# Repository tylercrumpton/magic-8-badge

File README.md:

# Magic 8-Badge

_Hardware, software, and other resouces for a fun little CircuitPython-compatible PCB badge!_

**Note:** Lots of information and improvements to be added soon!

## Hardware

All of the hardware design files are included in the [`hardware/`](./hardware) directory. The board was designed with KiCad 7, using mostly components from JLCPCB's [Assembly Parts Library](https://jlcpcb.com/parts).

## Firmware

The Magic 8-Badge was created to utilize [Adafruit's CircuitPython 🐍](https://circuitpython.org), and will hopefully have a board definition available on the CircuitPython website soon. The v1 version of the Magic 8-Badge distrbuted at PhreakNIC 24 in Nov 2023 are runnings a slightly-modified version of CircuitPython 8.2.0 that enables software pullup resistors on the I2C lines connected to the 6DoF IMU chip. The diff in changes in available in [`firmware/8.2.x-circuitpython-patch-208ebdf3.diff`](./firmware/8.2.x-circuitpython-patch-208ebdf3.diff).

The CircuitPython `*.py` files used to run the badge are included in [`firmware/circuitpy-code`](./firmware/circuitpy-code). This code is a huge mess, but I have some changes coming soon that will clean up the code, speed up the boot time, improve the UX and graphics a bit, and hopefully add more fun little features! The main application is found in [`firmware/circuitpy-code/code.py`](./firmware/circuitpy-code/code.py), and there are some required libraries that need to be installed from the Adafruit CircuitPython Bundle as well as the Community Bundle:

- Adafruit CircuitPython Bundle requirements:
  - `adafruit_display_text`
  - `adafruit_imageload`
- Community Bundle requirements:
  - `gc9a01`

You'll need to copy these libraries from the respective bundles into the `/lib` directory on the `CIRCUITPY` drive that should show up when plugged into a USB port on your computer.

## Errata

I will include notes her about board bugs, things to consider when making code changes, and whatever else little idiosyncasies are present in various versions of the Magic 8-Badge.

### v1

Version v1 of the Magic 8-Badge has a couple of issues that are mostly worked around in software and hardware re-work:

- The QMC6308 magnetometer chip (U9) has been removed from all v1 boards because the power and ground connections are reversed. If the chip is placed, the board will fail to start, effectively shorting the 3v3 power rail. Don't do this!
- There are no external pullups on the I2C lines connected to the QMI8658C accelerometer/gyroscope chip (U7). CircuitPython doesn't currently support setting internal pullup resistors for I2C pins, and the internal pullup resistors on the RP2040 are technically out of spec for I2C communications (50-80kohms). The patch to the CircuitPython core described above manually enables the internal pullup resistors, and I've not seen any issues reading from the QMI8658C with those. I'm going to try to submit a pull request to allow compile-time enabling of these internal resistors so that a custom build of CircuitPython is no longer neccessary. If you want to try a different version of CircuitPython that doesn't include that patch, no harm will be done, but CircuitPython will throw an error when trying to connect to the QMI8658C.
- There is no low-voltage cut-off for the Li-ion battery used for the Magic 8-Badge. The battery selected does offer low-voltage protection to keep the battery from discharging to dangerous levels, but the threshold voltage is lower than I would have liked. I recommend disconnecting the Li-ion battery if it is not going to be used in order preserve the capacity and health of the battery.

## License

The hardware and its design files are licensed under the [CERN Open Hardware Licence v2 - Permissive](./hardware/LICENSE.TXT).

The firmware/software is licensed under the [MIT License](./firmware/LICENSE.TXT).

The CrumpSpace logo is a trademark of CrumpSpace and should not be used in association with hardware or software that is sold or distributed by others.

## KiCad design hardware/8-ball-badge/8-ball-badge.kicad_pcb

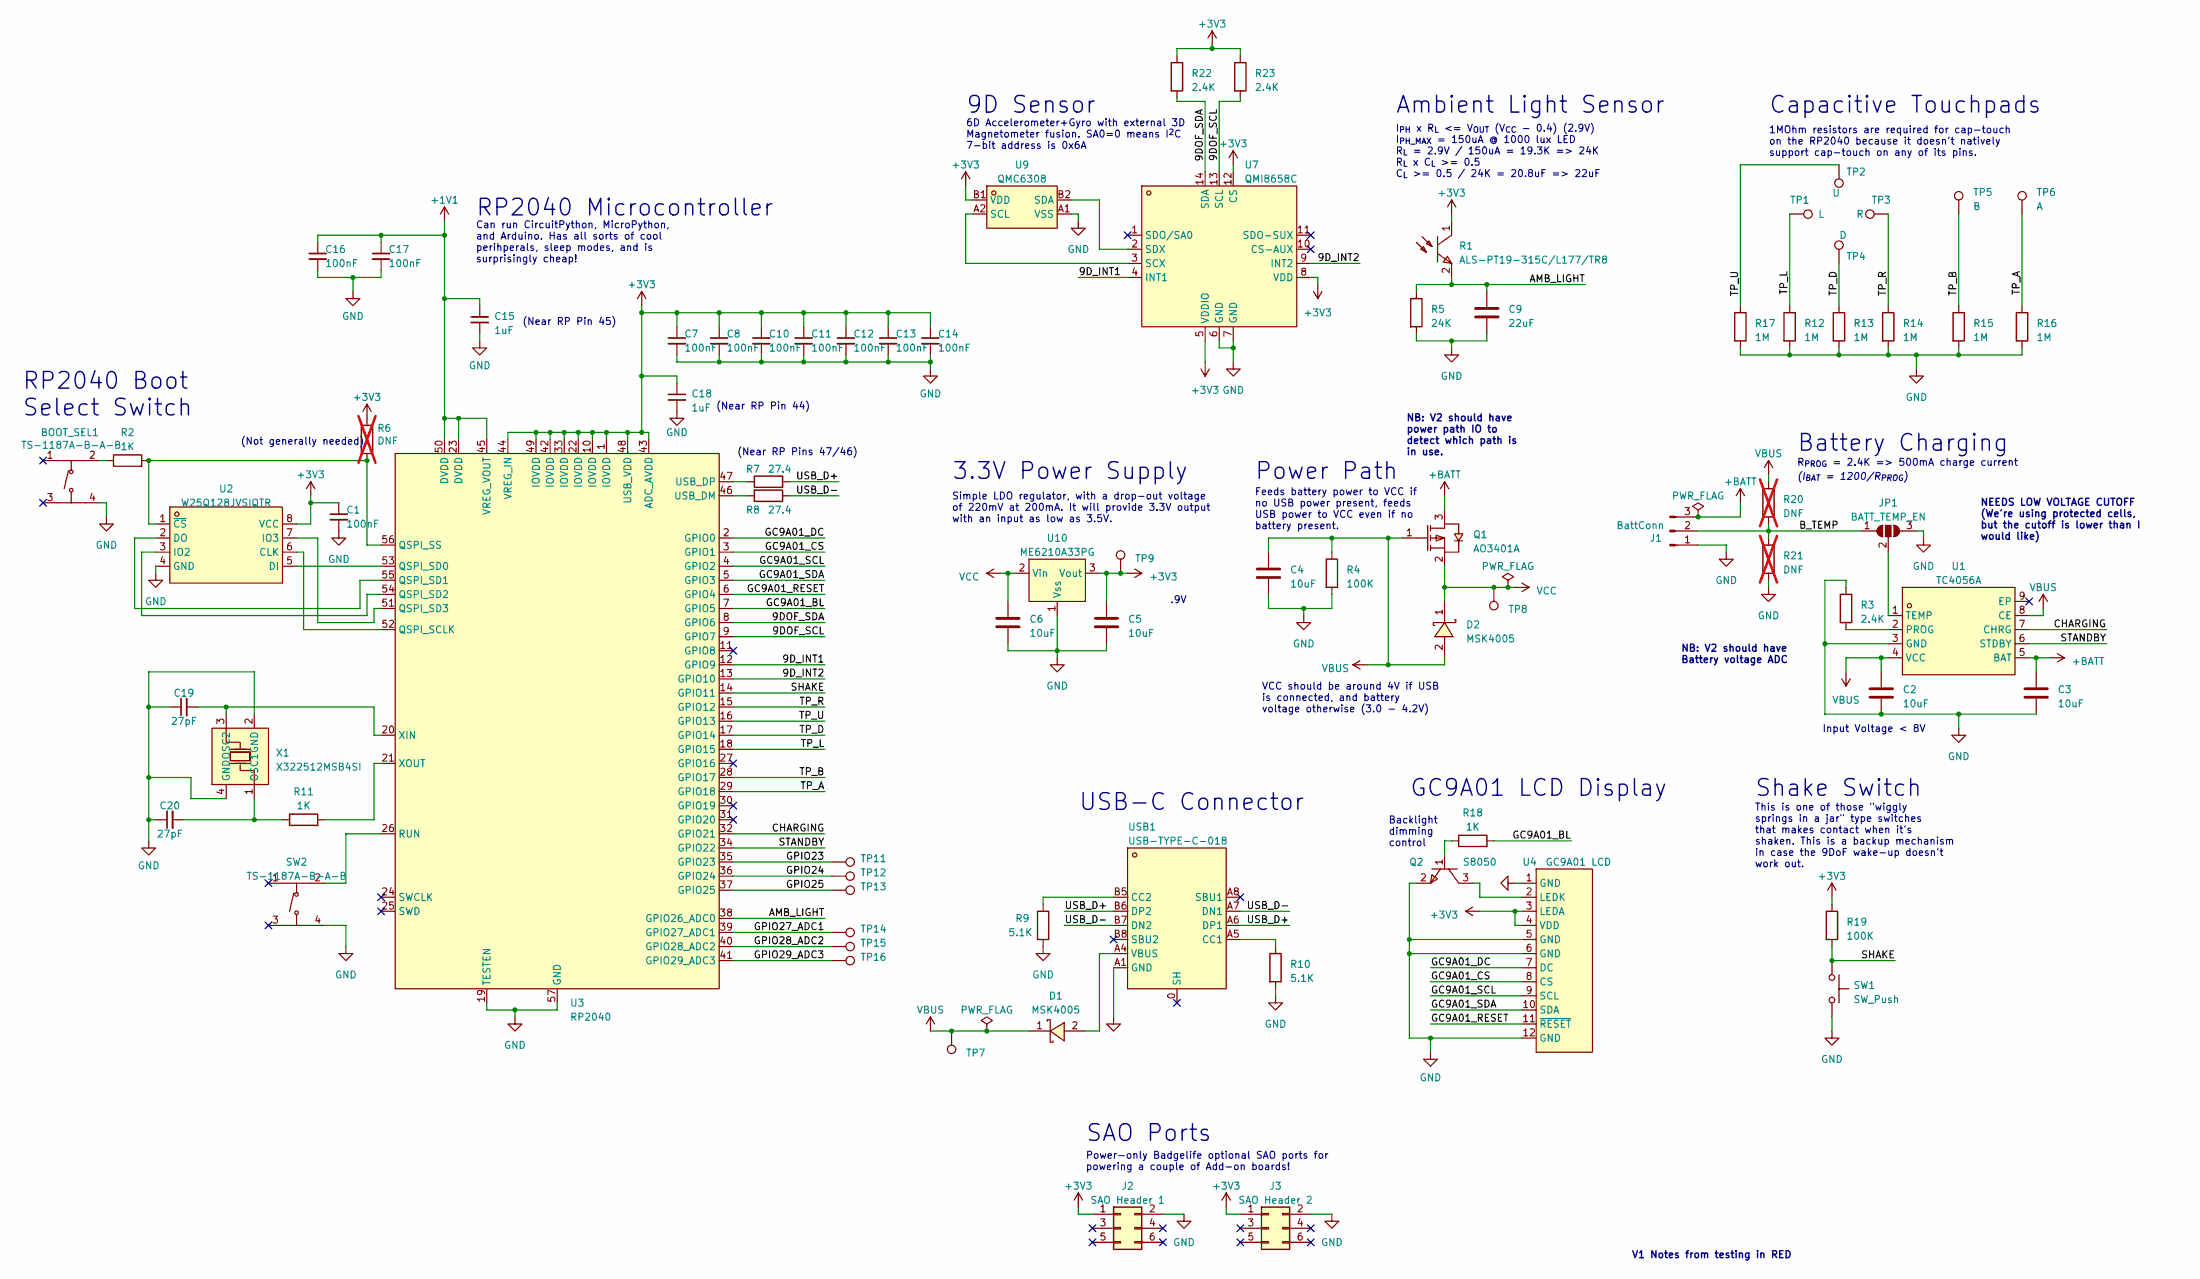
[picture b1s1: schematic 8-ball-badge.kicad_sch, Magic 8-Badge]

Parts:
BOOT_SEL1: TS-1187A-B-A-B; SW-SMD_4P-L5.1-W5.1-P3.70-LS6.5-TL-2; LCSC Part C318884
C1, C7, C8, C10, C11, C12, C13, C14, C16, C17: 100nF; C_0603_1608Metric_Pad1.08x0.95mm_HandSolder; LCSC Part # C14663
C2, C3, C4, C5, C6: 10uF; C_0603_1608Metric_Pad1.08x0.95mm_HandSolder; LCSC Part # C19702
C9: 22uF; C_0603_1608Metric_Pad1.08x0.95mm_HandSolder; LCSC Part # C59461
C15, C18: 1uF; C_0603_1608Metric_Pad1.08x0.95mm_HandSolder; LCSC Part # C15849
C19, C20: 27pF; C_0603_1608Metric_Pad1.08x0.95mm_HandSolder; LCSC Part # C302064
D1, D2: MSK4005; SOD-523F_L1.2-W0.8-LS1.7-RD; LCSC Part C345957
J1: BattConn; CONN-TH_3P-P1.25_HDGC_HDGC1251WR-3P
J2: SAO Header 1; Badgelife-SAOv169-BADGE-2x3
J3: SAO Header 2; Badgelife-SAOv169-BADGE-2x3
JP1: BATT_TEMP_EN; SolderJumper-3_P1.3mm_Open_RoundedPad1.0x1.5mm
Q1: AO3401A; SOT-23_L2.9-W1.3-P1.90-LS2.4-BR; LCSC Part C15127
Q2: S8050; SOT-23-3_L3.0-W1.7-P0.95-LS2.9-BR; LCSC Part C2146
R1: ALS-PT19-315C/L177/TR8; SENSORS-SMD_ALS-PT19; LCSC Part # C146233
R2, R11, R18: 1K; R_0603_1608Metric_Pad0.98x0.95mm_HandSolder; LCSC Part # C21190
R3, R22, R23: 2.4K; R_0603_1608Metric_Pad0.98x0.95mm_HandSolder; LCSC Part # C22940
R4, R19: 100K; R_0603_1608Metric_Pad0.98x0.95mm_HandSolder; LCSC Part # C25803
R5: 24K; R_0603_1608Metric_Pad0.98x0.95mm_HandSolder; LCSC Part # C23352
R6: DNF; R_0603_1608Metric_Pad0.98x0.95mm_HandSolder; not fitted
R7, R8: 27.4; R_0603_1608Metric_Pad0.98x0.95mm_HandSolder; LCSC Part # C100926
R9, R10: 5.1K; R_0603_1608Metric_Pad0.98x0.95mm_HandSolder; LCSC Part # C23186
R12, R13, R14, R15, R16, R17: 1M; R_0603_1608Metric_Pad0.98x0.95mm_HandSolder; LCSC Part # C22935
R20, R21: DNF; C_0603_1608Metric_Pad1.08x0.95mm_HandSolder; not fitted
SW1: SW_Push; PinHeader_1x02_P2.54mm_Horizontal
SW2: TS-1187A-B-A-B; SW-SMD_4P-L5.1-W5.1-P3.70-LS6.5-TL-2; LCSC Part C318884
TP1: L; chip_left
TP2: U; chip_up
TP3: R; chip_r
TP4: D; chip_down
TP5: B; chip_b
TP6: A; chip_a
TP7, TP8, TP9, TP11, TP12, TP13, TP14, TP15, TP16: TestPoint; TestPoint_Pad_D1.0mm
U1: TC4056A; ESOP-8_L4.9-W3.9-P1.27-LS6.0-BR-EP3.3; LCSC Part # C84051
U2: W25Q128JVSIQTR; SOIC-8_L5.3-W5.3-P1.27-LS8.0-BL; LCSC Part C97521
U3: RP2040; LQFN-56_L7.0-W7.0-P0.4-EP; LCSC Part C2040
U4: GC9A01 LCD; GC9A01
U7: QMI8658C; LGA-14_L3.0-W2.5-P0.50-BR; LCSC Part # C2842151
U9: QMC6308; WLCSP-4_L0.8-W0.8-R2-C2-P0.40-BL; LCSC Part C462705
U10: ME6210A33PG; SOT-89_L4.5-W2.5-P1.50-LS4.2-BR; LCSC Part C85233
USB1: USB-TYPE-C-018; USB-C_SMD-TYPE-C-31-M-12; LCSC Part C2927038
X1: X322512MSB4SI; OSC-SMD_4P-L3.2-W2.5-BL; LCSC Part C9002

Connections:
+1V1: C15.1, C16.1, C17.1, U3.23 (DVDD), U3.45 (VREG_VOUT), U3.50 (DVDD)
+3V3: C1.1, C5.1, C7.1, C8.1, C10.1, C11.1, C12.1, C13.1, C14.1, C18.1, J2.1, J3.1, R1.1, R6.1, R19.1, R22.1, R23.1, TP9.1, U2.8 (VCC), U3.1 (IOVDD), U3.10 (IOVDD), U3.22 (IOVDD), U3.33 (IOVDD), U3.42 (IOVDD), U3.43 (ADC_AVDD), U3.44 (VREG_IN), U3.48 (USB_VDD), U3.49 (IOVDD), U4.3 (LEDA), U4.4 (VDD), U7.5 (VDDIO), U7.8 (VDD), U7.12 (CS), U9.B1 (VDD), U10.3 (Vout)
+BATT: C3.1, J1.3, Q1.3, U1.5 (BAT)
/9DOF_SCL: R23.2, U3.9 (GPIO7), U7.13 (SCL)
/9DOF_SDA: R22.2, U3.8 (GPIO6), U7.14 (SDA)
/9D_INT1: U3.12 (GPIO9), U7.4 (INT1)
/9D_INT2: U3.13 (GPIO10), U7.9 (INT2)
/AMB_LIGHT: C9.1, R1.2, R5.1, U3.38 (GPIO26_ADC0)
/B_TEMP: J1.2, JP1.1 (A), R20.2, R21.1
/CHARGING: U1.7 (CHRG), U3.32 (GPIO21)
/GC9A01_BL: R18.2, U3.7 (GPIO5)
/GC9A01_CS: U3.3 (GPIO1), U4.8 (CS)
/GC9A01_DC: U3.2 (GPIO0), U4.7 (DC)
/GC9A01_RESET: U3.6 (GPIO4), U4.11 (~RESET)
/GC9A01_SCL: U3.4 (GPIO2), U4.9 (SCL)
/GC9A01_SDA: U3.5 (GPIO3), U4.10 (SDA)
/GPIO23: TP11.1, U3.35 (GPIO23)
/GPIO24: TP12.1, U3.36 (GPIO24)
/GPIO25: TP13.1, U3.37 (GPIO25)
/GPIO27_ADC1: TP14.1, U3.39 (GPIO27_ADC1)
/GPIO28_ADC2: TP15.1, U3.40 (GPIO28_ADC2)
/GPIO29_ADC3: TP16.1, U3.41 (GPIO29_ADC3)
/SHAKE: R19.2, SW1.1, U3.14 (GPIO11)
/STANDBY: U1.6 (STDBY), U3.34 (GPIO22)
/TP_A: R16.1, TP6.1, U3.29 (GPIO18)
/TP_B: R15.1, TP5.1, U3.28 (GPIO17)
/TP_D: R13.1, TP4.1, U3.17 (GPIO14)
/TP_L: R12.1, TP1.1, U3.18 (GPIO15)
/TP_R: R14.1, TP3.1, U3.15 (GPIO12)
/TP_U: R17.1, TP2.1, U3.16 (GPIO13)
/USB_D+: R7.2, USB1.A6 (DP1), USB1.B6 (DP2)
/USB_D-: R8.1, USB1.A7 (DN1), USB1.B7 (DN2)
GND: BOOT_SEL1.4, C1.2, C2.2, C3.2, C4.2, C5.2, C6.2, C7.2, C8.2, C9.2, C10.2, C11.2, C12.2, C13.2, C14.2, C15.2, C16.2, C17.2, C18.2, C19.1, C20.1, J1.1, J2.2, J3.2, JP1.3 (B), Q2.2, R3.1, R4.2, R5.2, R9.2, R10.2, R12.2, R13.2, R14.2, R15.2, R16.2, R17.2, R21.2, SW1.2, SW2.4, U1.3 (GND), U2.4 (GND), U3.19 (TESTEN), U3.57 (GND), U4.1 (GND), U4.5 (GND), U4.6 (GND), U4.12 (GND), U7.6 (GND), U7.7 (GND), U9.A1 (VSS), U10.1 (Vss), USB1.A1 (GND), USB1.A12 (GND), USB1.B1 (GND), USB1.B12 (GND), X1.2 (GND), X1.4 (GND)
unnamed: BOOT_SEL1.2, R2.1
unnamed: D1.2, USB1.A4 (VBUS), USB1.A9 (VBUS), USB1.B4 (VBUS), USB1.B9 (VBUS)
unnamed: JP1.2 (C), U1.1 (TEMP)
unnamed: Q2.1, R18.1
unnamed: R3.2, U1.2 (PROG)
unnamed: U2.6 (CLK), U3.52 (QSPI_SCLK)
unnamed: U2.5 (DI), U3.53 (QSPI_SD0)
unnamed: U2.2 (DO), U3.55 (QSPI_SD1)
unnamed: U2.3 (IO2), U3.54 (QSPI_SD2)
unnamed: U2.7 (IO3), U3.51 (QSPI_SD3)
unnamed: R2.2, R6.2, U2.1 (~CS), U3.56 (QSPI_SS)
unnamed: SW2.2, U3.26 (RUN)
unnamed: R8.2, U3.46 (USB_DM)
unnamed: R7.1, U3.47 (USB_DP)
unnamed: C19.2, U3.20 (XIN), X1.3 (OSC2)
unnamed: R11.2, U3.21 (XOUT)
unnamed: Q2.3, U4.2 (LEDK)
unnamed: U7.3 (SCX), U9.A2 (SCL)
unnamed: U7.2 (SDX), U9.B2 (SDA)
unnamed: R10.1, USB1.A5 (CC1)
unnamed: R9.1, USB1.B5 (CC2)
unnamed: C20.2, R11.1, X1.1 (OSC1)
VBUS: C2.1, C4.1, D1.1, D2.2, Q1.1, R4.1, R20.1, TP7.1, U1.4 (VCC), U1.8 (CE)
VCC: C6.1, D2.1, Q1.2, TP8.1, U10.2 (Vin)

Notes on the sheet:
I_{PH} x R_{L} <= V_{OUT} (V_{CC} - 0.4) (2.9V) I_{PH_MAX} = 150uA @ 1000 lux LED R_{L} = 2.9V / 150uA = 19.3K => 24K R_{L} x C_{L} >= 0.5 C_{L} >= 0.5 / 24K = 20.8uF => 22uF
Power Path
USB-C Connector
(Not generally needed)
(Near RP Pin 45)
Battery Charging
(I_{BAT} = 1200/R_{PROG})
1MOhm resistors are required for cap-touch on the RP2040 because it doesn't natively support cap-touch on any of its pins.
NB: V2 should have power path IO to detect which path is in use.
Input Voltage < 8V
Can run CircuitPython, MicroPython, and Arduino. Has all sorts of cool perihperals, sleep modes, and is surprisingly cheap!
R_{PROG} = 2.4K => 500mA charge current
Power-only Badgelife optional SAO ports for powering a couple of Add-on boards!
RP2040 Boot Select Switch
Shake Switch
9D Sensor
.9V
GC9A01 LCD Display
Simple LDO regulator, with a drop-out voltage of 220mV at 200mA. It will provide 3.3V output with an input as low as 3.5V.
SAO Ports
NB: V2 should have Battery voltage ADC
(Near RP Pins 47/46)
RP2040 Microcontroller
VCC should be around 4V if USB is connected, and battery voltage otherwise (3.0 - 4.2V)
Capacitive Touchpads
Feeds battery power to VCC if no USB power present, feeds USB power to VCC even if no battery present.
Ambient Light Sensor
3.3V Power Supply
Backlight dimming control
V1 Notes from testing in RED
NEEDS LOW VOLTAGE CUTOFF (We're using protected cells, but the cutoff is lower than I would like)
This is one of those "wiggly springs in a jar" type switches that makes contact when it's shaken. This is a backup mechanism in case the 9DoF wake-up doesn't work out.
6D Accelerometer+Gyro with external 3D Magnetometer fusion. SA0=0 means I^{2}C 7-bit address is 0x6A
(Near RP Pin 44)

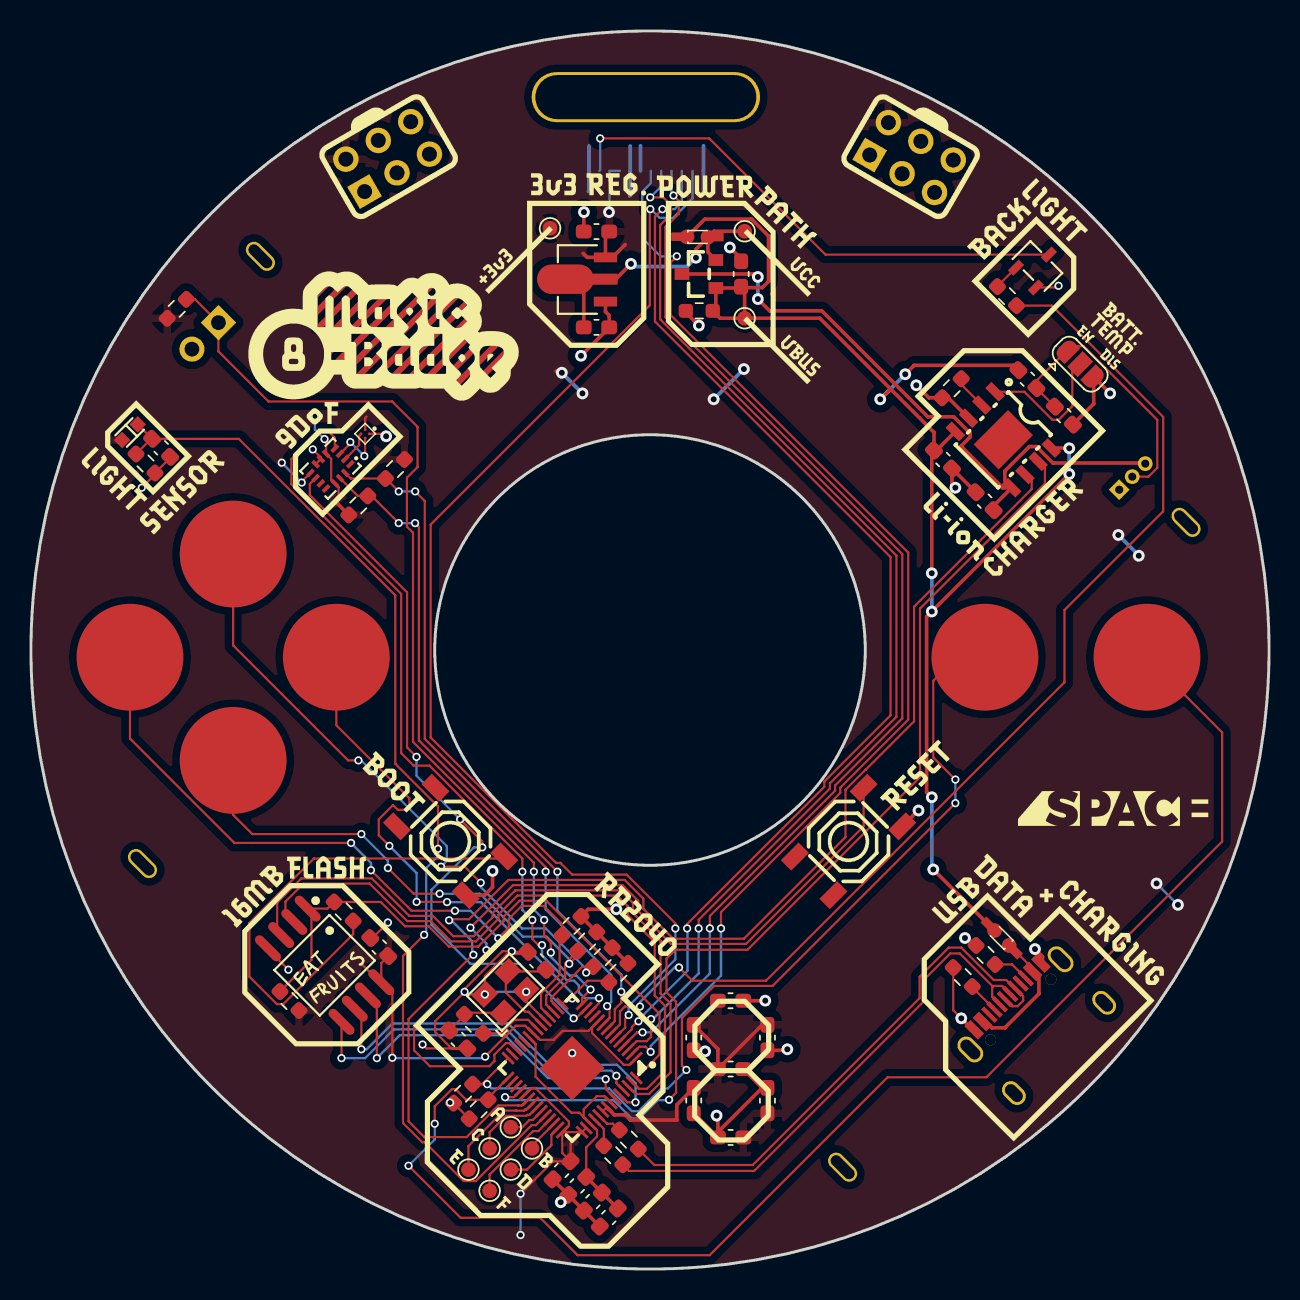
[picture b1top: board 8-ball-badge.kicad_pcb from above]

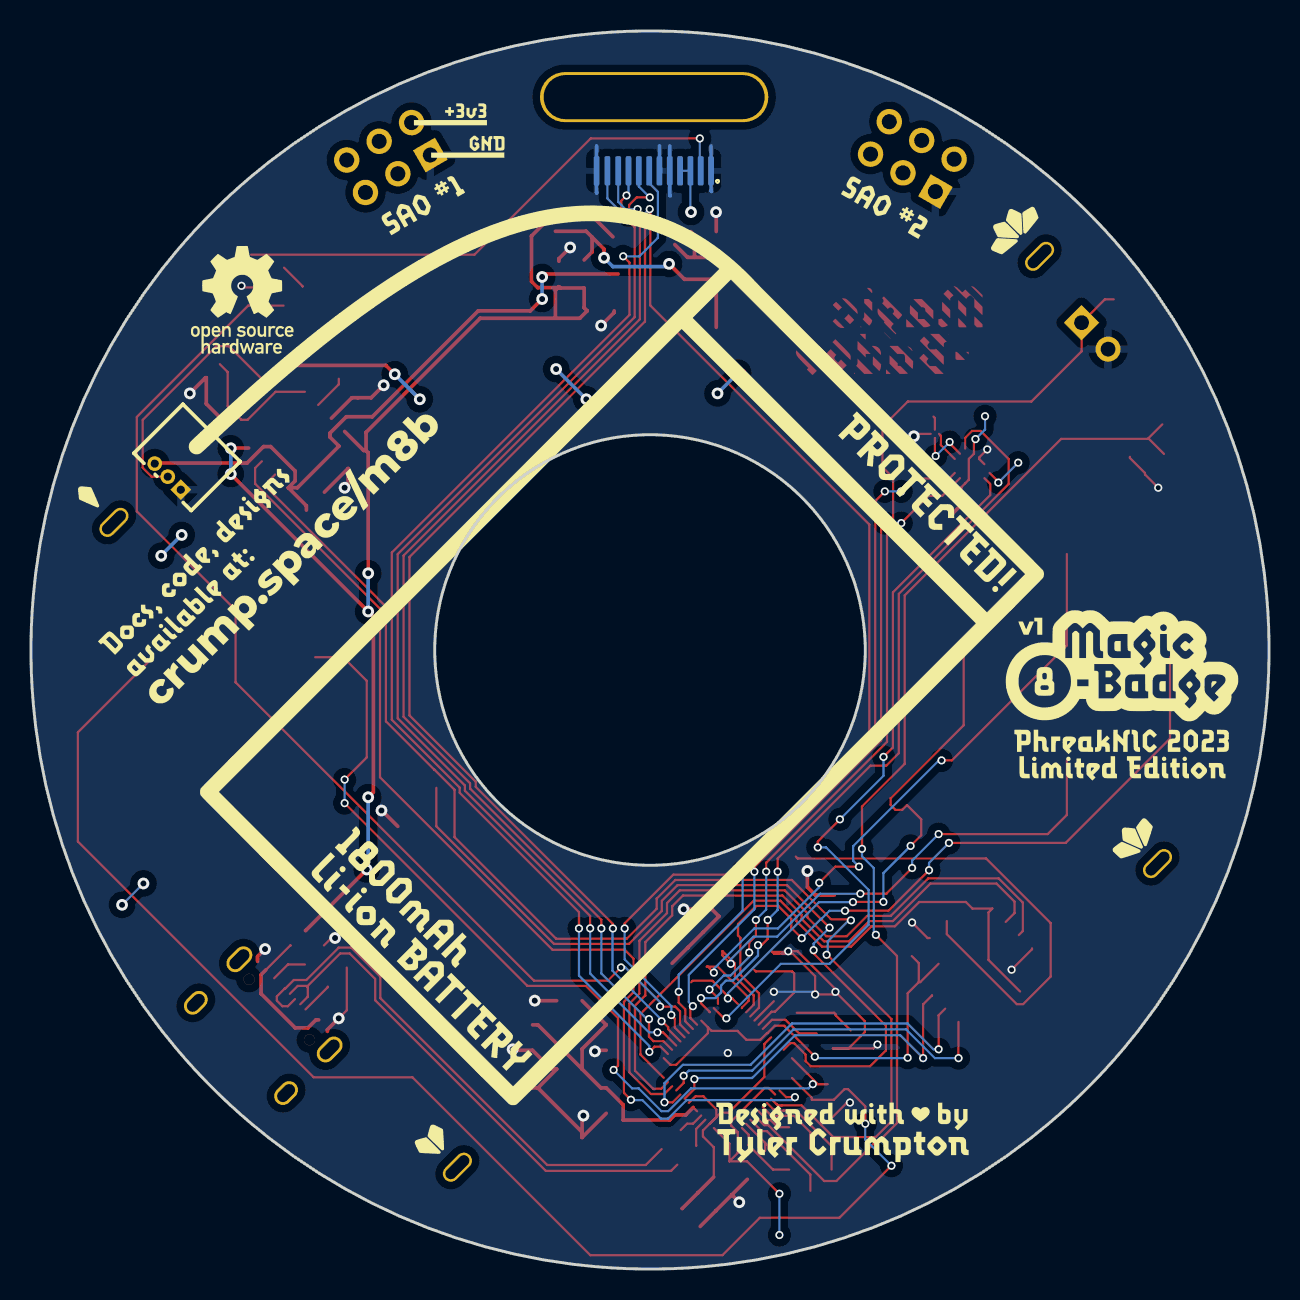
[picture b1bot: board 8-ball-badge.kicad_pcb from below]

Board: 2 copper layers, 84.0 x 84.0 mm, 78 parts (2 on the bottom side), 57 nets.

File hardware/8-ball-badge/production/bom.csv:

Designator,Footprint,Quantity,Value,LCSC Part #
"BOOT_SEL1, SW2",SW-SMD_4P-L5.1-W5.1-P3.70-LS6.5-TL-2,2,TS-1187A-B-A-B,C318884
"C1, C10, C11, C12, C13, C14, C16, C17, C7, C8",0603,10,100nF,C14663
"C15, C18",0603,2,1uF,C15849
"C19, C20",0603,2,27pF,C302064
"C2, C3, C4, C5, C6",0603,5,10uF,C19702
C9,0603,1,22uF,C59461
"D1, D2",SOD-523F_L1.2-W0.8-LS1.7-RD,2,MSK4005,C345957
J1,CONN-TH_3P-P1.25_HDGC_HDGC1251WR-3P,1,BattConn,
J2,Badgelife-SAOv169-BADGE-2x3,1,SAO Header 1,
J3,Badgelife-SAOv169-BADGE-2x3,1,SAO Header 2,
JP1,SolderJumper-3_P1.3mm_Open_RoundedPad1.0x1.5mm,1,BATT_TEMP_EN,
Q1,SOT-23_L2.9-W1.3-P1.90-LS2.4-BR,1,AO3401A,C15127
Q2,SOT-23-3_L3.0-W1.7-P0.95-LS2.9-BR,1,S8050,C2146
R1,SENSORS-SMD_ALS-PT19,1,ALS-PT19-315C/L177/TR8,C146233
"R10, R9",0603,2,5.1K,C23186
"R11, R18, R2",0603,3,1K,C21190
"R12, R13, R14, R15, R16, R17",0603,6,1M,C22935
"R19, R4",0603,2,100K,C25803
"R20, R21, R6",0603,3,DNF,
R3,0603,1,2.4K,C22940
R5,0603,1,24K,C23352
"R7, R8",0603,2,27.4,C100926
SW1,PinHeader_1x02_P2.54mm_Horizontal,1,SW_Push,
TP1,chip_left,1,L,
"TP11, TP12, TP13, TP14, TP15, TP16, TP7, TP8, TP9",TestPoint_Pad_D1.0mm,9,TestPoint,
TP2,chip_up,1,U,
TP3,chip_r,1,R,
TP4,chip_down,1,D,
TP5,chip_b,1,B,
TP6,chip_a,1,A,
U1,ESOP-8_L4.9-W3.9-P1.27-LS6.0-BR-EP3.3,1,TC4056A,C84051
U10,SOT-89_L4.5-W2.5-P1.50-LS4.2-BR,1,ME6210A33PG,C85233
U2,SOIC-8_L5.3-W5.3-P1.27-LS8.0-BL,1,W25Q128JVSIQTR,C97521
U3,LQFN-56_L7.0-W7.0-P0.4-EP,1,RP2040,C2040
U4,GC9A01,1,GC9A01 LCD,
U7,LGA-14_L3.0-W2.5-P0.50-BR,1,QMI8658C,C2842151
U9,WLCSP-4_L0.8-W0.8-R2-C2-P0.40-BL,1,QMC6308,C462705
USB1,USB-C_SMD-TYPE-C-31-M-12,1,USB-TYPE-C-018,C2927038
X1,OSC-SMD_4P-L3.2-W2.5-BL,1,X322512MSB4SI,C9002

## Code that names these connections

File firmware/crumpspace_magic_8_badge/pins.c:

#include "shared-bindings/board/__init__.h"

STATIC const mp_rom_map_elem_t board_module_globals_table[] = {
    CIRCUITPYTHON_BOARD_DICT_STANDARD_ITEMS

    { MP_ROM_QSTR(MP_QSTR_SHAKE), MP_ROM_PTR(&pin_GPIO11) },
    { MP_ROM_QSTR(MP_QSTR_CHARGING), MP_ROM_PTR(&pin_GPIO21) },
    { MP_ROM_QSTR(MP_QSTR_STANDBY), MP_ROM_PTR(&pin_GPIO22) },
    { MP_ROM_QSTR(MP_QSTR_TOUCH_RIGHT), MP_ROM_PTR(&pin_GPIO12) },
    { MP_ROM_QSTR(MP_QSTR_TOUCH_UP), MP_ROM_PTR(&pin_GPIO13) },
    { MP_ROM_QSTR(MP_QSTR_TOUCH_DOWN), MP_ROM_PTR(&pin_GPIO14) },
    { MP_ROM_QSTR(MP_QSTR_TOUCH_LEFT), MP_ROM_PTR(&pin_GPIO15) },
    { MP_ROM_QSTR(MP_QSTR_TOUCH_A), MP_ROM_PTR(&pin_GPIO18) },
    { MP_ROM_QSTR(MP_QSTR_TOUCH_B), MP_ROM_PTR(&pin_GPIO17) },
    { MP_ROM_QSTR(MP_QSTR_LIGHT_SENSOR), MP_ROM_PTR(&pin_GPIO26) },

    { MP_ROM_QSTR(MP_QSTR_LCD_DC), MP_ROM_PTR(&pin_GPIO0) },
    { MP_ROM_QSTR(MP_QSTR_LCD_CS), MP_ROM_PTR(&pin_GPIO1) },
    { MP_ROM_QSTR(MP_QSTR_LCD_SCL), MP_ROM_PTR(&pin_GPIO2) },
    { MP_ROM_QSTR(MP_QSTR_LCD_SDA), MP_ROM_PTR(&pin_GPIO3) },
    { MP_ROM_QSTR(MP_QSTR_LCD_RESET), MP_ROM_PTR(&pin_GPIO4) },
    { MP_ROM_QSTR(MP_QSTR_LCD_BACKLIGHT), MP_ROM_PTR(&pin_GPIO5) },

    { MP_ROM_QSTR(MP_QSTR_IMU_SDA), MP_ROM_PTR(&pin_GPIO6) },
    { MP_ROM_QSTR(MP_QSTR_IMU_SCL), MP_ROM_PTR(&pin_GPIO7) },
    { MP_ROM_QSTR(MP_QSTR_IMU_INT1), MP_ROM_PTR(&pin_GPIO9) },
    { MP_ROM_QSTR(MP_QSTR_IMU_INT2), MP_ROM_PTR(&pin_GPIO10) },

    { MP_ROM_QSTR(MP_QSTR_IMU_I2C), MP_ROM_PTR(&board_i2c_obj) },
};
MP_DEFINE_CONST_DICT(board_module_globals, board_module_globals_table);

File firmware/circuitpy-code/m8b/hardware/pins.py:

import board


class Touch:
    A = board.TOUCH_A
    B = board.TOUCH_B
    UP = board.TOUCH_UP
    DOWN = board.TOUCH_DOWN
    LEFT = board.TOUCH_LEFT
    RIGHT = board.TOUCH_RIGHT


TOUCH_PINS = [Touch.A, Touch.B, Touch.UP, Touch.DOWN, Touch.LEFT, Touch.RIGHT]

LIGHT_SENSOR_PIN = board.LIGHT_SENSOR
CHARGING_PIN = board.CHARGING
STANDBY_PIN = board.STANDBY
SHAKE_PIN = board.SHAKE
BACKLIGHT_PIN = board.LCD_BACKLIGHT

IMU_I2C = board.IMU_I2C()

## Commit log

2023-10-30 Add v1 hardware design files
2023-10-30 Add board def and hacks for i2c pullups
2023-10-30 Add initial circuitpy scripts and libs
2023-11-01 Make circuitpy script more production
2023-11-05 First pass at README
2023-11-05 Fix link formatting
2023-11-05 Add v1 errata and notes
2023-12-04 Add licensing information
2023-12-04 Fix some typos in the README
2023-12-04 Add image to README
2023-12-04 Fix issues with 9DoF chip
2023-12-04 Update mfg outputs
2024-02-24 Refactor the engine to be much easier to use
2024-02-24 Add IMU and Touch Test apps
2024-02-24 Add quit label for m8b app
2024-02-28 Add sleep
2024-02-28 Quit on hold release
2024-02-28 Add charger hardware support
2024-02-28 Add initial backlight control
2024-02-28 Trim trailing whitespace
2024-02-28 Formatting
2024-02-28 Add backlight controller helper and test app

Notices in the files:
hardware/8-ball-badge/8-ball-badge.kicad_sch:
Copyright Tyler Crumpton, 2023
Licensed under CERN-OHL-P version 2
